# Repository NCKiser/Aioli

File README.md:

# Aioli
3x3 Macropad with 9 Encoders or MX Switches

GPL 2, Open Source, Please credit [Noah Kiser, KiserDesigns.com]

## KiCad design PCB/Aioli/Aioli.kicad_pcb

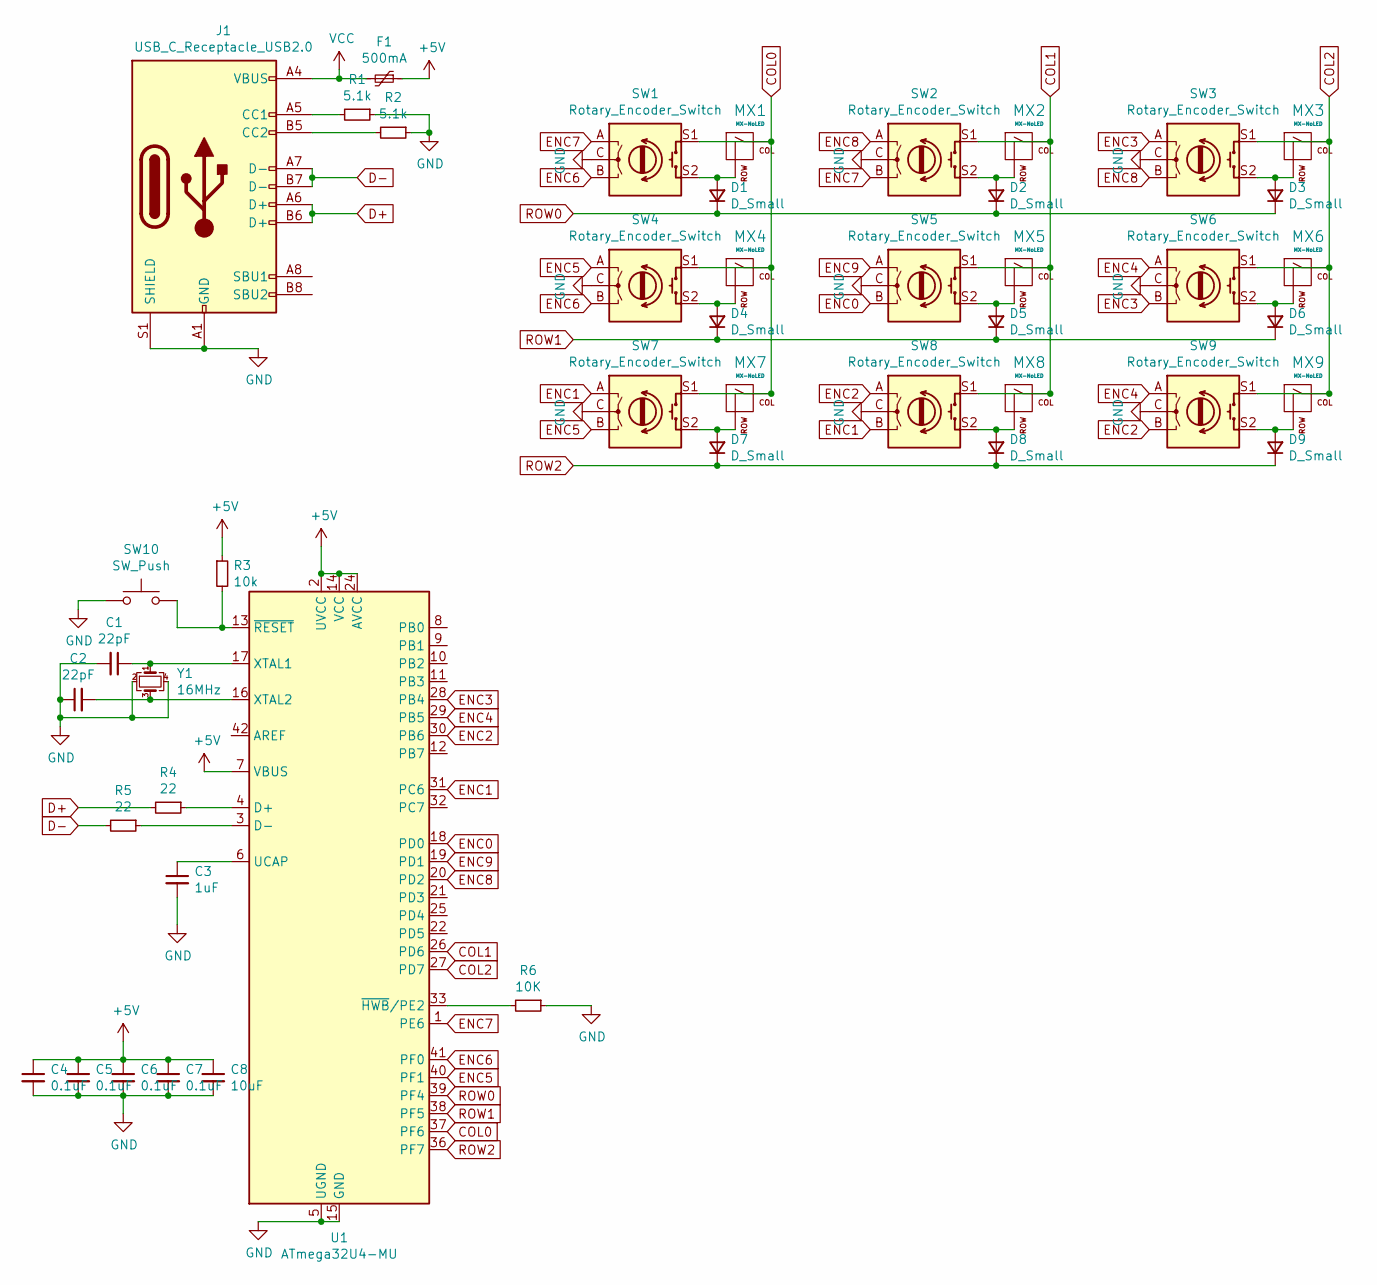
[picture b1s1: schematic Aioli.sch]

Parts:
C1, C2: 22pF; C_0603_1608Metric_Pad1.08x0.95mm_HandSolder
C3: 1uF; C_0603_1608Metric_Pad1.08x0.95mm_HandSolder
C4, C5, C6, C7: 0.1uF; C_0603_1608Metric_Pad1.08x0.95mm_HandSolder
C8: 10uF; C_0603_1608Metric_Pad1.08x0.95mm_HandSolder
D1, D2, D3, D4, D5, D6, D7, D8, D9: D_Small; D_SOD-123
F1: 500mA; Fuse_1206_3216Metric
J1: USB_C_Receptacle_USB2.0; USB_C_Receptacle_HRO_TYPE-C-31-M-12
MX1, MX2, MX3, MX4, MX5, MX6, MX7, MX8, MX9: MX-NoLED; MXOnly-1U-NoLED
R1, R2: 5.1k; R_0603_1608Metric_Pad0.98x0.95mm_HandSolder
R3: 10k; R_0603_1608Metric_Pad0.98x0.95mm_HandSolder
R4, R5: 22; R_0603_1608Metric_Pad0.98x0.95mm_HandSolder
R6: 10K; R_0603_1608Metric_Pad0.98x0.95mm_HandSolder
SW1, SW2, SW3, SW4, SW5, SW6, SW7, SW8, SW9: Rotary_Encoder_Switch; RotaryEncoder_Alps_EC11E-Switch_Vertical_H20mm
SW10: SW_Push; SKQG-1155865
U1: ATmega32U4-MU; QFN-44-1EP_7x7mm_P0.5mm_EP5.2x5.2mm
Y1: 16MHz; Crystal_SMD_3225-4Pin_3.2x2.5mm

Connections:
+5V: C4.1, C5.1, C6.1, C7.1, C8.1, F1.1, R3.1, U1.2 (UVCC), U1.7 (VBUS), U1.14 (VCC), U1.24 (AVCC), U1.34 (VCC), U1.44 (AVCC)
COL0: MX1.1 (COL), MX4.1 (COL), MX7.1 (COL), SW1.S1, SW4.S1, SW7.S1, U1.37 (PF6)
COL1: MX2.1 (COL), MX5.1 (COL), MX8.1 (COL), SW2.S1, SW5.S1, SW8.S1, U1.26 (PD6)
COL2: MX3.1 (COL), MX6.1 (COL), MX9.1 (COL), SW3.S1, SW6.S1, SW9.S1, U1.27 (PD7)
D+: J1.A6 (D+), J1.B6 (D+), R4.2
D-: J1.A7 (D-), J1.B7 (D-), R5.2
ENC0: SW5.B, U1.18 (PD0)
ENC1: SW7.A, SW8.B, U1.31 (PC6)
ENC2: SW8.A, SW9.B, U1.30 (PB6)
ENC3: SW3.A, SW6.B, U1.28 (PB4)
ENC4: SW6.A, SW9.A, U1.29 (PB5)
ENC5: SW4.A, SW7.B, U1.40 (PF1)
ENC6: SW1.B, SW4.B, U1.41 (PF0)
ENC7: SW1.A, SW2.B, U1.1 (PE6)
ENC8: SW2.A, SW3.B, U1.20 (PD2)
ENC9: SW5.A, U1.19 (PD1)
GND: C1.2, C2.1, C3.2, C4.2, C5.2, C6.2, C7.2, C8.2, J1.A1 (GND), J1.A12 (GND), J1.B1 (GND), J1.B12 (GND), J1.S1 (SHIELD), R1.1, R2.1, R6.1, SW1.C, SW2.C, SW3.C, SW4.C, SW5.C, SW6.C, SW7.C, SW8.C, SW9.C, SW10.1, U1.5 (UGND), U1.15 (GND), U1.23 (GND), U1.35 (GND), U1.43 (GND), U1.45 (GND), Y1.2, Y1.4
unnamed: C1.1, U1.17 (XTAL1), Y1.1
unnamed: C2.2, U1.16 (XTAL2), Y1.3
unnamed: C3.1, U1.6 (UCAP)
unnamed: D1.2 (A), MX1.2 (ROW), SW1.S2
unnamed: D2.2 (A), MX2.2 (ROW), SW2.S2
unnamed: D3.2 (A), MX3.2 (ROW), SW3.S2
unnamed: D4.2 (A), MX4.2 (ROW), SW4.S2
unnamed: D5.2 (A), MX5.2 (ROW), SW5.S2
unnamed: D6.2 (A), MX6.2 (ROW), SW6.S2
unnamed: D7.2 (A), MX7.2 (ROW), SW7.S2
unnamed: D8.2 (A), MX8.2 (ROW), SW8.S2
unnamed: D9.2 (A), MX9.2 (ROW), SW9.S2
unnamed: J1.A5 (CC1), R1.2
unnamed: J1.B5 (CC2), R2.2
unnamed: R3.2, SW10.2, U1.13 (~RESET)
unnamed: R4.1, U1.4 (D+)
unnamed: R5.1, U1.3 (D-)
unnamed: R6.2, U1.33 (~HWB~/PE2)
ROW0: D1.1 (K), D2.1 (K), D3.1 (K), U1.39 (PF4)
ROW1: D4.1 (K), D5.1 (K), D6.1 (K), U1.38 (PF5)
ROW2: D7.1 (K), D8.1 (K), D9.1 (K), U1.36 (PF7)
VCC: F1.2, J1.A4 (VBUS), J1.A9 (VBUS), J1.B4 (VBUS), J1.B9 (VBUS)

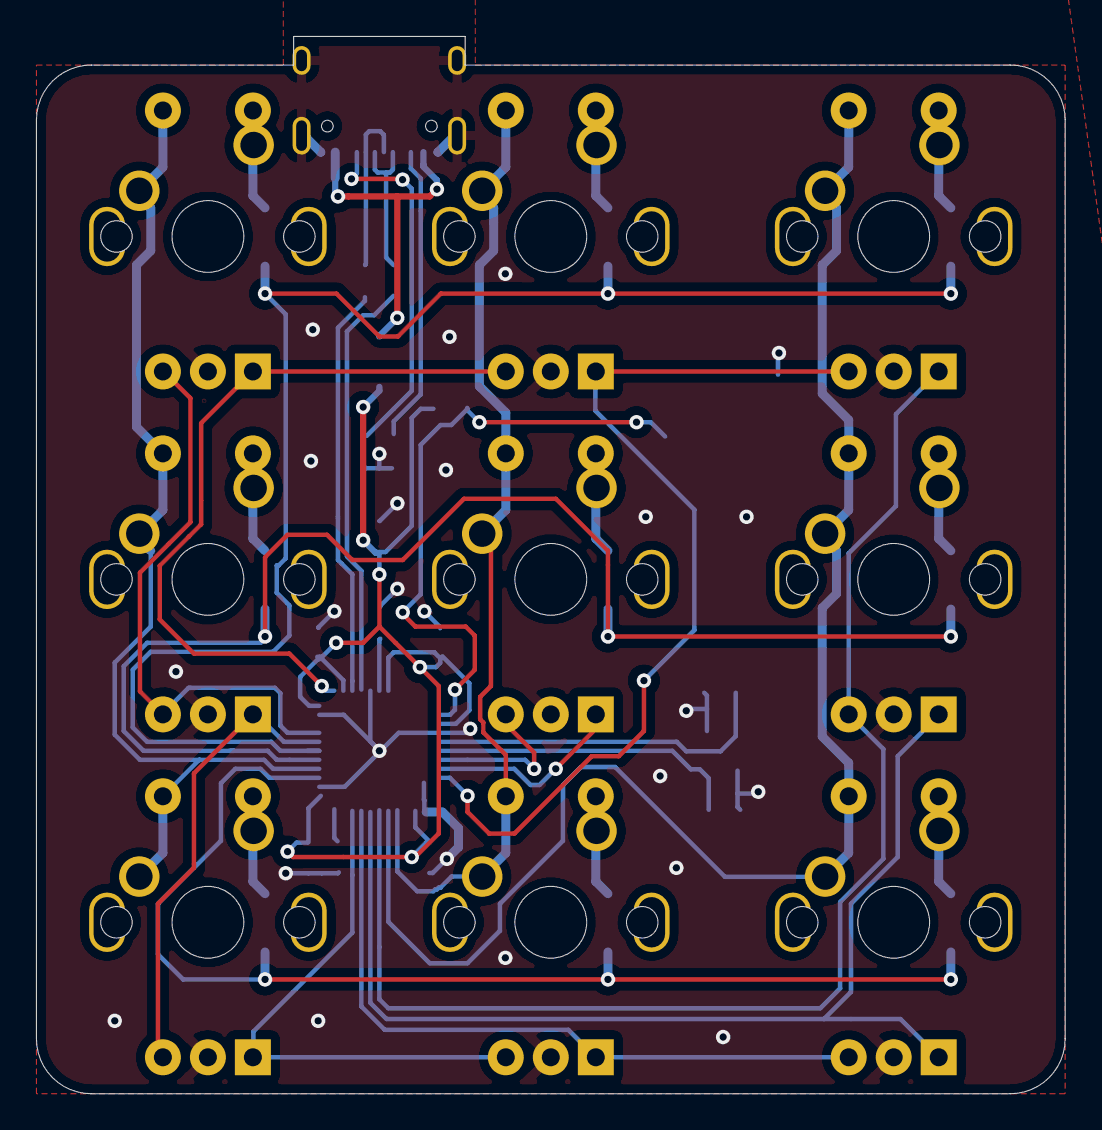
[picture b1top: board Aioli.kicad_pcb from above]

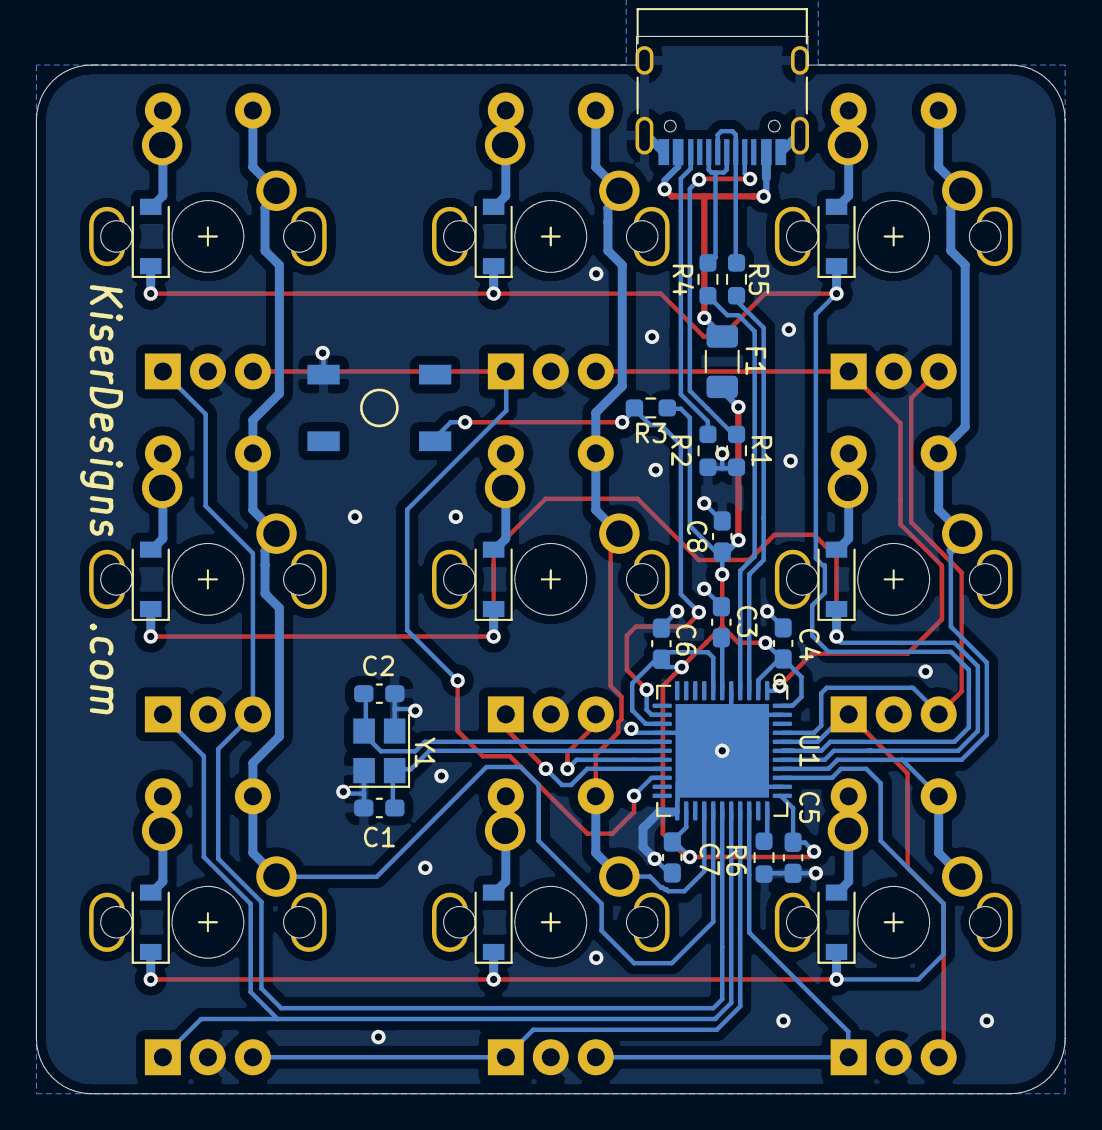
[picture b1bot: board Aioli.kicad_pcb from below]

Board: 2 copper layers, 57.1 x 58.7 mm, 46 parts (37 on the bottom side), 39 nets.

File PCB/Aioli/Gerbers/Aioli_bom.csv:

Comment,Designator,Footprint,LCSC Part Number
ATmega32U4-MU,U1,QFN-44-1EP_7x7mm_P0.5mm_EP5.2x5.2mm,C45874
SW_Push,SW10,SKQG-1155865,C127478
10K,R6,R_0603_1608Metric_Pad0.98x0.95mm_HandSolder,C25804
22 ohm,"R5,R4",R_0603_1608Metric_Pad0.98x0.95mm_HandSolder,C23345
10k,R3,R_0603_1608Metric_Pad0.98x0.95mm_HandSolder,C25804
5.1k,"R2,R1",R_0603_1608Metric_Pad0.98x0.95mm_HandSolder,C23186
10uF,C8,C_0603_1608Metric_Pad1.08x0.95mm_HandSolder,C19702
0.1uF,"C7,C6,C5,C4",C_0603_1608Metric_Pad1.08x0.95mm_HandSolder,C14663
1uF,C3,C_0603_1608Metric_Pad1.08x0.95mm_HandSolder,C15849
22pF,"C2,C1",C_0603_1608Metric_Pad1.08x0.95mm_HandSolder,C1653
16MHz,Y1,Crystal_SMD_3225-4Pin_3.2x2.5mm,C13738
USB_C_Receptacle_USB2.0,J1,USB_C_Receptacle_HRO_TYPE-C-31-M-12,C165948
500mA,F1,Fuse_1206_3216Metric,C70076
D_Small,"D9,D8,D7,D6,D5,D4,D3,D2,D1",D_SOD-123,C81598

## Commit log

2022-02-03 Created PCB
2022-02-06 Subtle Changes
2022-03-29 Generated Gerbers, CAD files
